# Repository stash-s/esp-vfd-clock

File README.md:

VFD clock driver on esp8266 chip.

See eagle subdirectory for device schematics.

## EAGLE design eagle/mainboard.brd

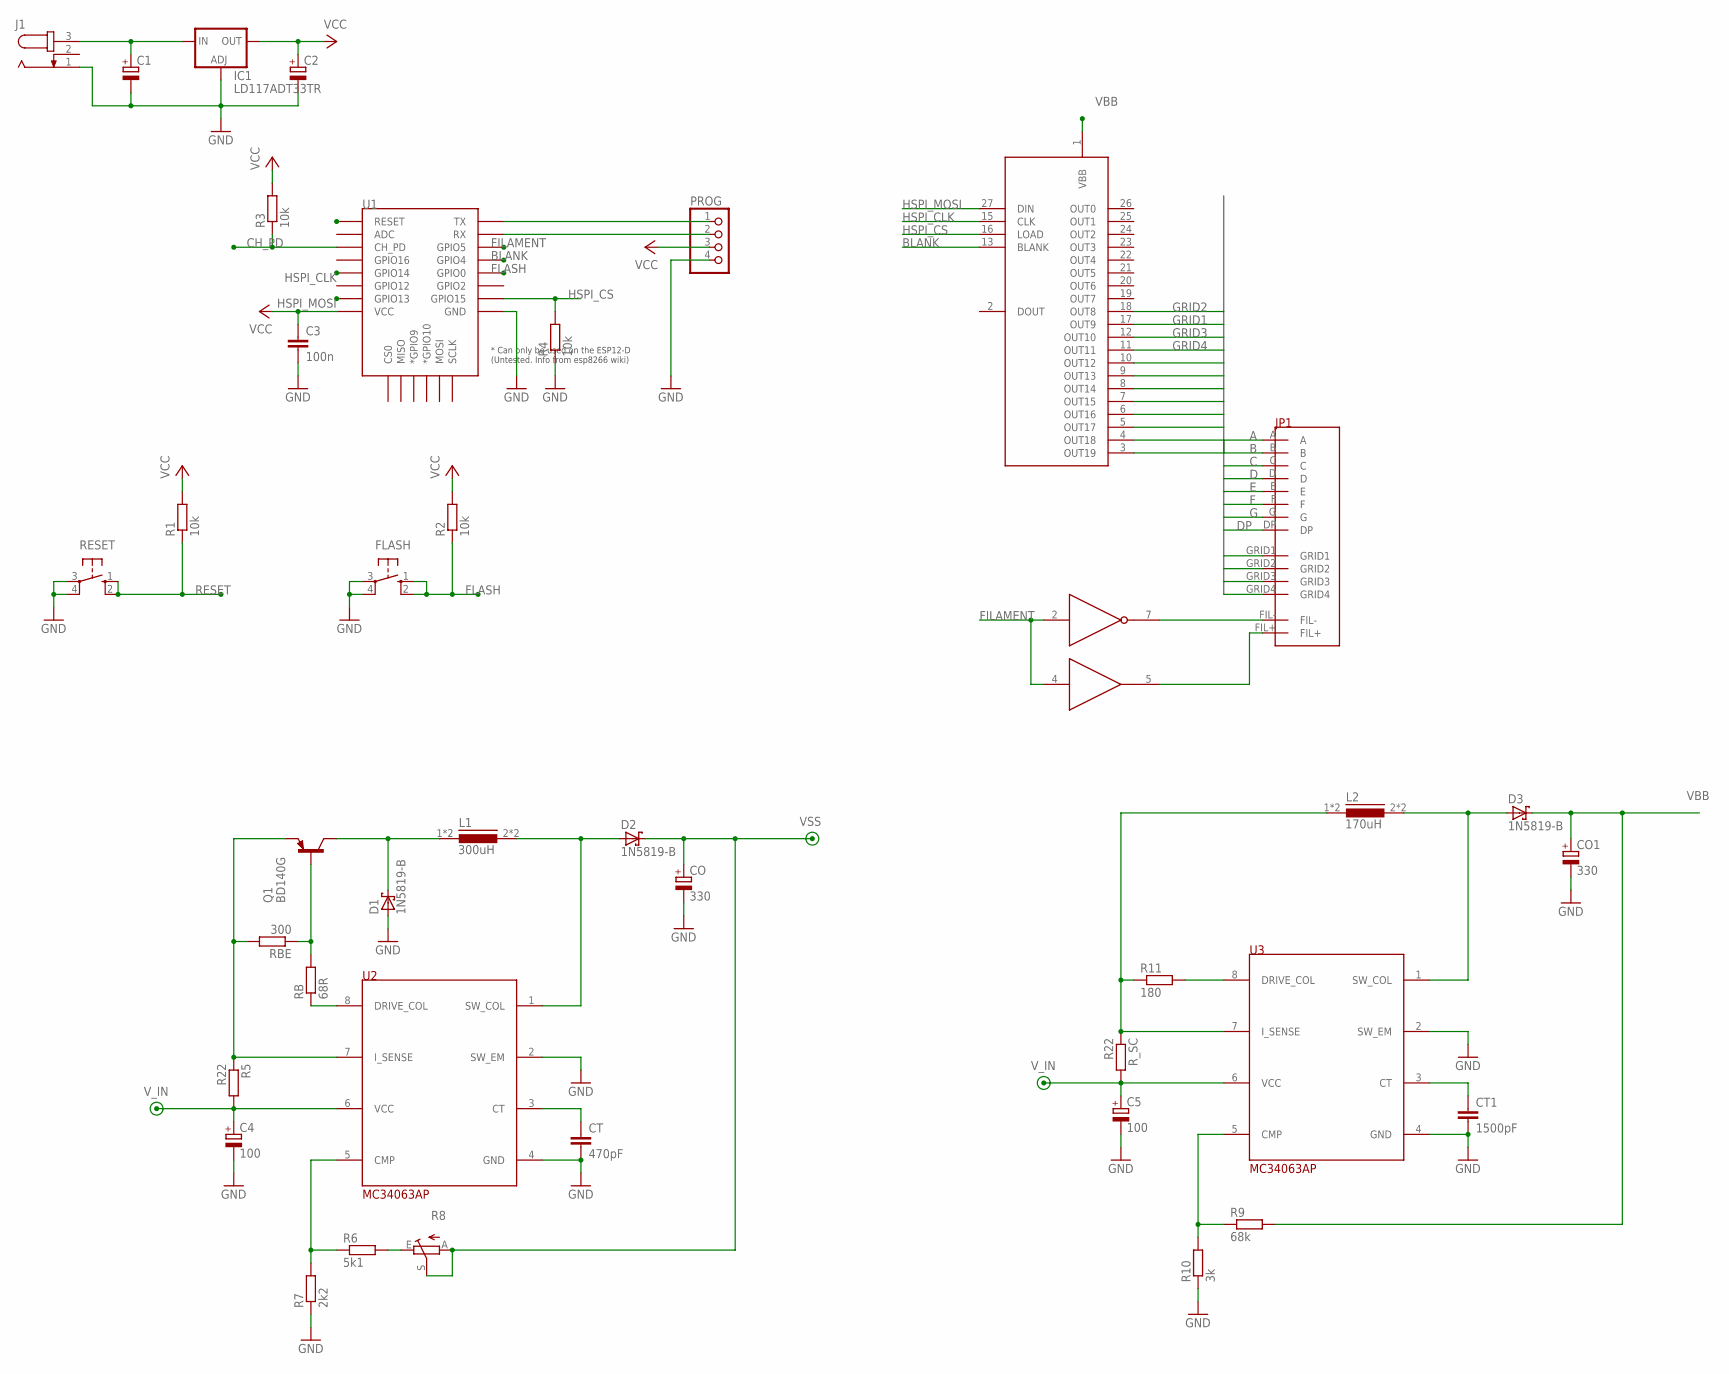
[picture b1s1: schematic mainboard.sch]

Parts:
C1, C2: CPOL-EUTT2D5L; TT2D5L
C3: 100n; C050-024X044
C4, C5: 100; TT2D5L
CO: 330; TT5D11R
CO1: 330; TT5D11L
CT: 470pF; C025-025X050
CT1: 1500pF; C025-025X050
D1, D2, D3: 1N5819-B; DO41-7.6
FLASH: 10-XX; B3F-10XX
IC1: LD117ADT33TR; DPACK
J1: JACK-PLUG0; SPC4077
JP1: PINHD-2X102X10-MALE; 2X10
L1: 300uH; TOROID
L2: 170uH; TOROID
PROG: PINHD-1X4/90; 1X04/90
Q1: BD140G; TO225AA
R1: 10k; 0207/12
R2, R4: 10k; 0204/7
R3: 10k; 0207/10
R5: R22; 0411/15
R6: 5k1; 0204/7
R7: 2k2; 0204/7
R8: TRIM_EU-S64W; S64W
R9: 68k; 0204/7
R10: 3k; 0204/7
R11: 180; 0204/7
RB: 68R; 0204/7
RBE: 300; 0204/7
RESET: 10-XX; B3F-10XX
R_SC: R22; 0411/15
U1: ESP12ESMD; ESP12E-SMD
U2, U3: MC34063AP; DIL8
U$1: MAX6921AWI; SOP28X
U$2: MAX628; DIL8

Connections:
A: JP1.A, U$1.10 (OUT12)
B: JP1.B, U$1.9 (OUT13)
BLANK: U1.GPIO4, U$1.13 (BLANK)
C: JP1.C, U$1.8 (OUT14)
CH_PD: R3.1, U1.CH_PD
D: JP1.D, U$1.7 (OUT15)
DP: JP1.DP, U$1.3 (OUT19)
E: JP1.E, U$1.6 (OUT16)
F: JP1.F, U$1.5 (OUT17)
FILAMENT: U1.GPIO5, U$2.2 (IN), U$2.4 (IN)
FLASH: FLASH.1 (S), FLASH.2 (S1), R2.1, U1.GPIO0
G: JP1.G, U$1.4 (OUT18)
GND: C1.-, C2.-, C3.2, C4.-, C5.-, CO.-, CO1.-, CT.2, CT1.2, D1.A, FLASH.3, FLASH.4 (P1), IC1.1 (ADJ), J1.1, PROG.4, R4.1, R7.1, R10.1, RESET.3, RESET.4 (P1), U1.GND, U2.2 (SW_EM), U2.4 (GND), U3.2 (SW_EM), U3.4 (GND), U$1.14 (GND), U$2.3 (GND)
GRID1: JP1.GRID1, U$1.17 (OUT9)
GRID2: JP1.GRID2, U$1.18 (OUT8)
GRID3: JP1.GRID3, U$1.12 (OUT10)
GRID4: JP1.GRID4, U$1.11 (OUT11)
HSPI_CLK: U1.GPIO14, U$1.15 (CLK)
HSPI_CS: R4.2, U1.GPIO15, U$1.16 (LOAD)
HSPI_MOSI: U1.GPIO13, U$1.27 (DIN)
unnamed: JP1.FIL-, U$2.7 (OUT)
unnamed: JP1.FIL+, U$2.5 (OUT)
unnamed: Q1.3 (B), RB.2, RBE.1
unnamed: RB.1, U2.8 (DRIVE_COL)
unnamed: Q1.1 (E), R5.1, RBE.2, U2.7 (I_SENSE)
unnamed: D2.A, L1.2, L1.2A (2), U2.1 (SW_COL)
unnamed: D1.C, L1.1, L1.1A (1), Q1.2 (C)
unnamed: CT.1, U2.3 (CT)
unnamed: R6.1, R7.2, U2.5 (CMP)
unnamed: R6.2, R8.E
unnamed: L2.1, L2.1A (1), R11.1, R_SC.1, U3.7 (I_SENSE)
unnamed: D3.A, L2.2, L2.2A (2), U3.1 (SW_COL)
unnamed: CT1.1, U3.3 (CT)
unnamed: R9.1, R10.2, U3.5 (CMP)
unnamed: R11.2, U3.8 (DRIVE_COL)
RESET: R1.1, RESET.1 (S), RESET.2 (S1), U1.RESET
RX: PROG.2, U1.RXD0 (RX)
TX: PROG.1, U1.TXD0 (TX)
VBB: CO1.+, D3.C, R9.2, U$1.1 (VBB)
VCC: C2.+, C3.1, IC1.4 (OUT), PROG.3, R1.2, R2.2, R3.2, U1.VCC, U$1.28 (VCC)
VSS: CO.+, D2.C, R8.A, R8.S, U$2.6 (VSS)
V_IN: C1.+, C4.+, C5.+, IC1.3 (IN), J1.3, R5.2, R_SC.2, U2.6 (VCC), U3.6 (VCC)

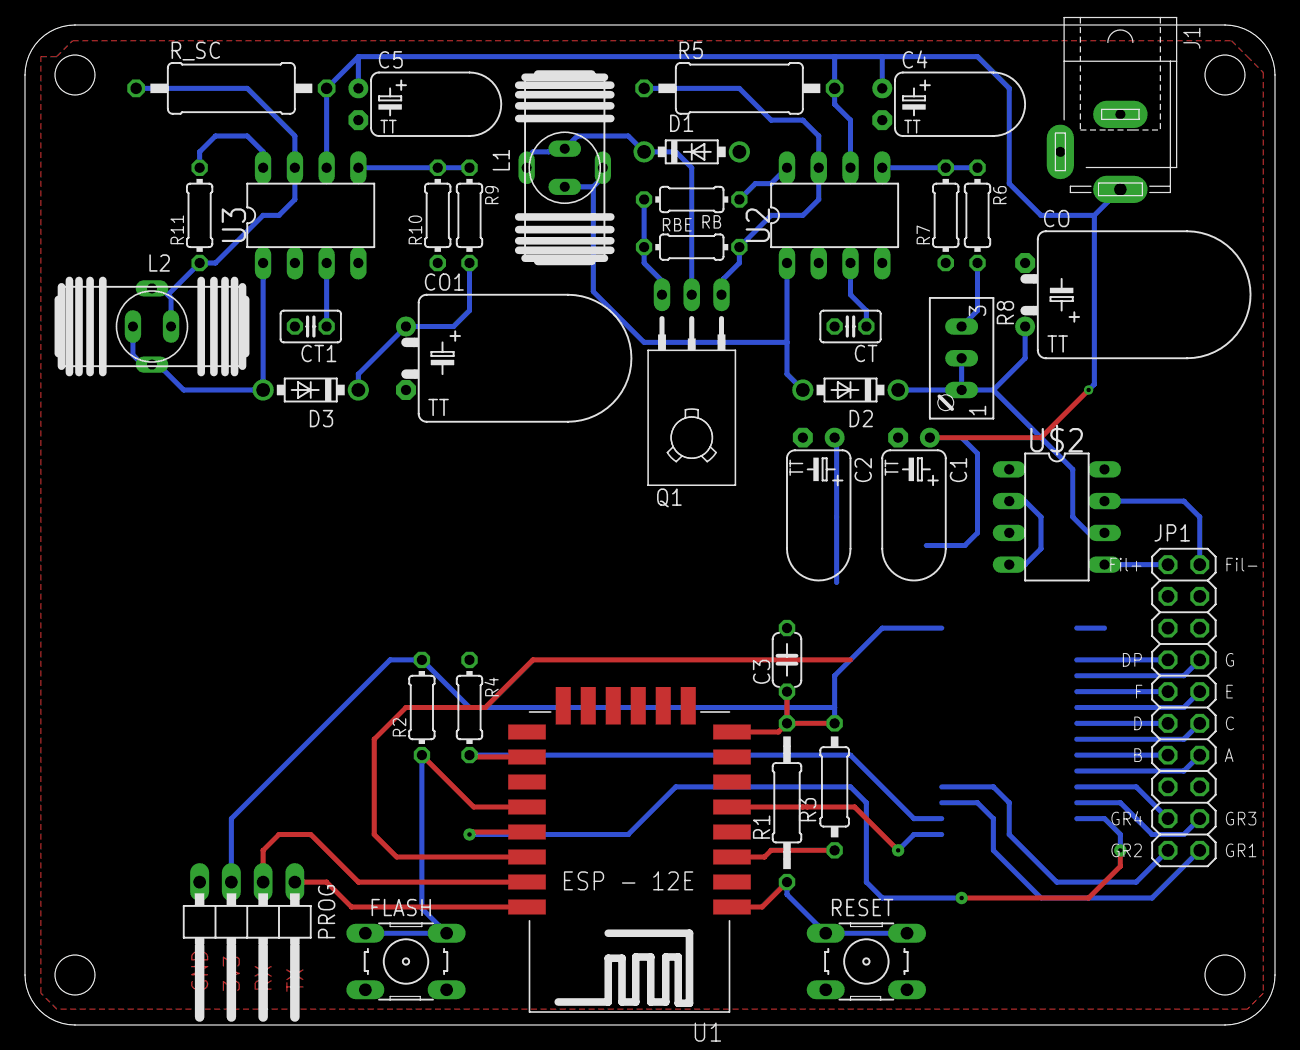
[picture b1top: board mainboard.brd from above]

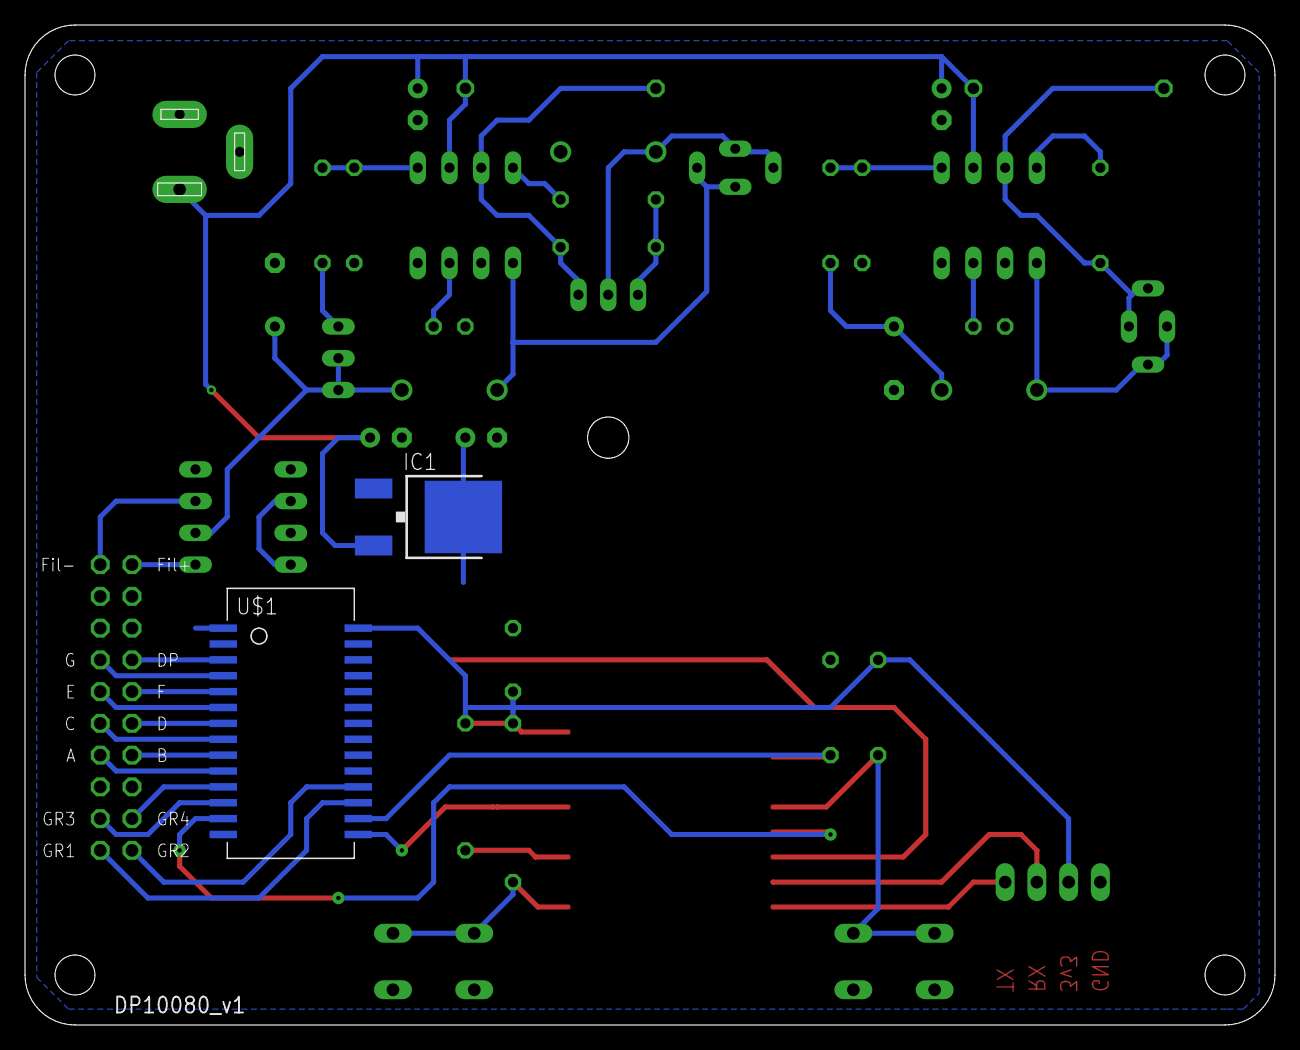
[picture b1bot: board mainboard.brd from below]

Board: 2 copper layers, 100.0 x 80.0 mm, 41 parts (2 on the bottom side), 42 nets.

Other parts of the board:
U$3: DP10080_V1

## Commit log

2018-01-06 Initial checkin of world's famous blinkey app.
2018-01-07 Added working SPI library.
2018-01-07 Moved SPI library to external dependency.
2018-01-08 Minor cleanup.
2018-01-08 Clock displays seconds and minutes. Ready for NTP!
2018-01-09 Working clock, getting time from NTP.
2018-01-11 Working clock with NTP support.
2018-02-11 Added eagle schemes and boards.
2018-02-12 Small documentation modification.
2018-04-01 Added light sensor support.
2018-05-11 Added vscode project
2018-05-11 Added vscode
2018-05-11 Removed compiler warning
2018-05-11 Set conding style to Google
2018-05-11 Set conding style
2018-10-28 Updated DST offset.
2022-11-16 Added workspace
